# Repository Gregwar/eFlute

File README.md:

# eFlute

**WARNING: This is still a work in progress, which is really poorly documented and with uncertain release date and evolution**

## Video

[Here is a video of an old version of the flute](https://www.youtube.com/watch?v=Vu05FvypGyI)

## License

This project is under CC-BY-NC license. If you're not sure about what you can
do, you should ask the author Grégoire Passault (g.passault@gmail.com).

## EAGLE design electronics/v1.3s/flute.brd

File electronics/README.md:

# Electronics

Here are (eagle) files to build the PCB

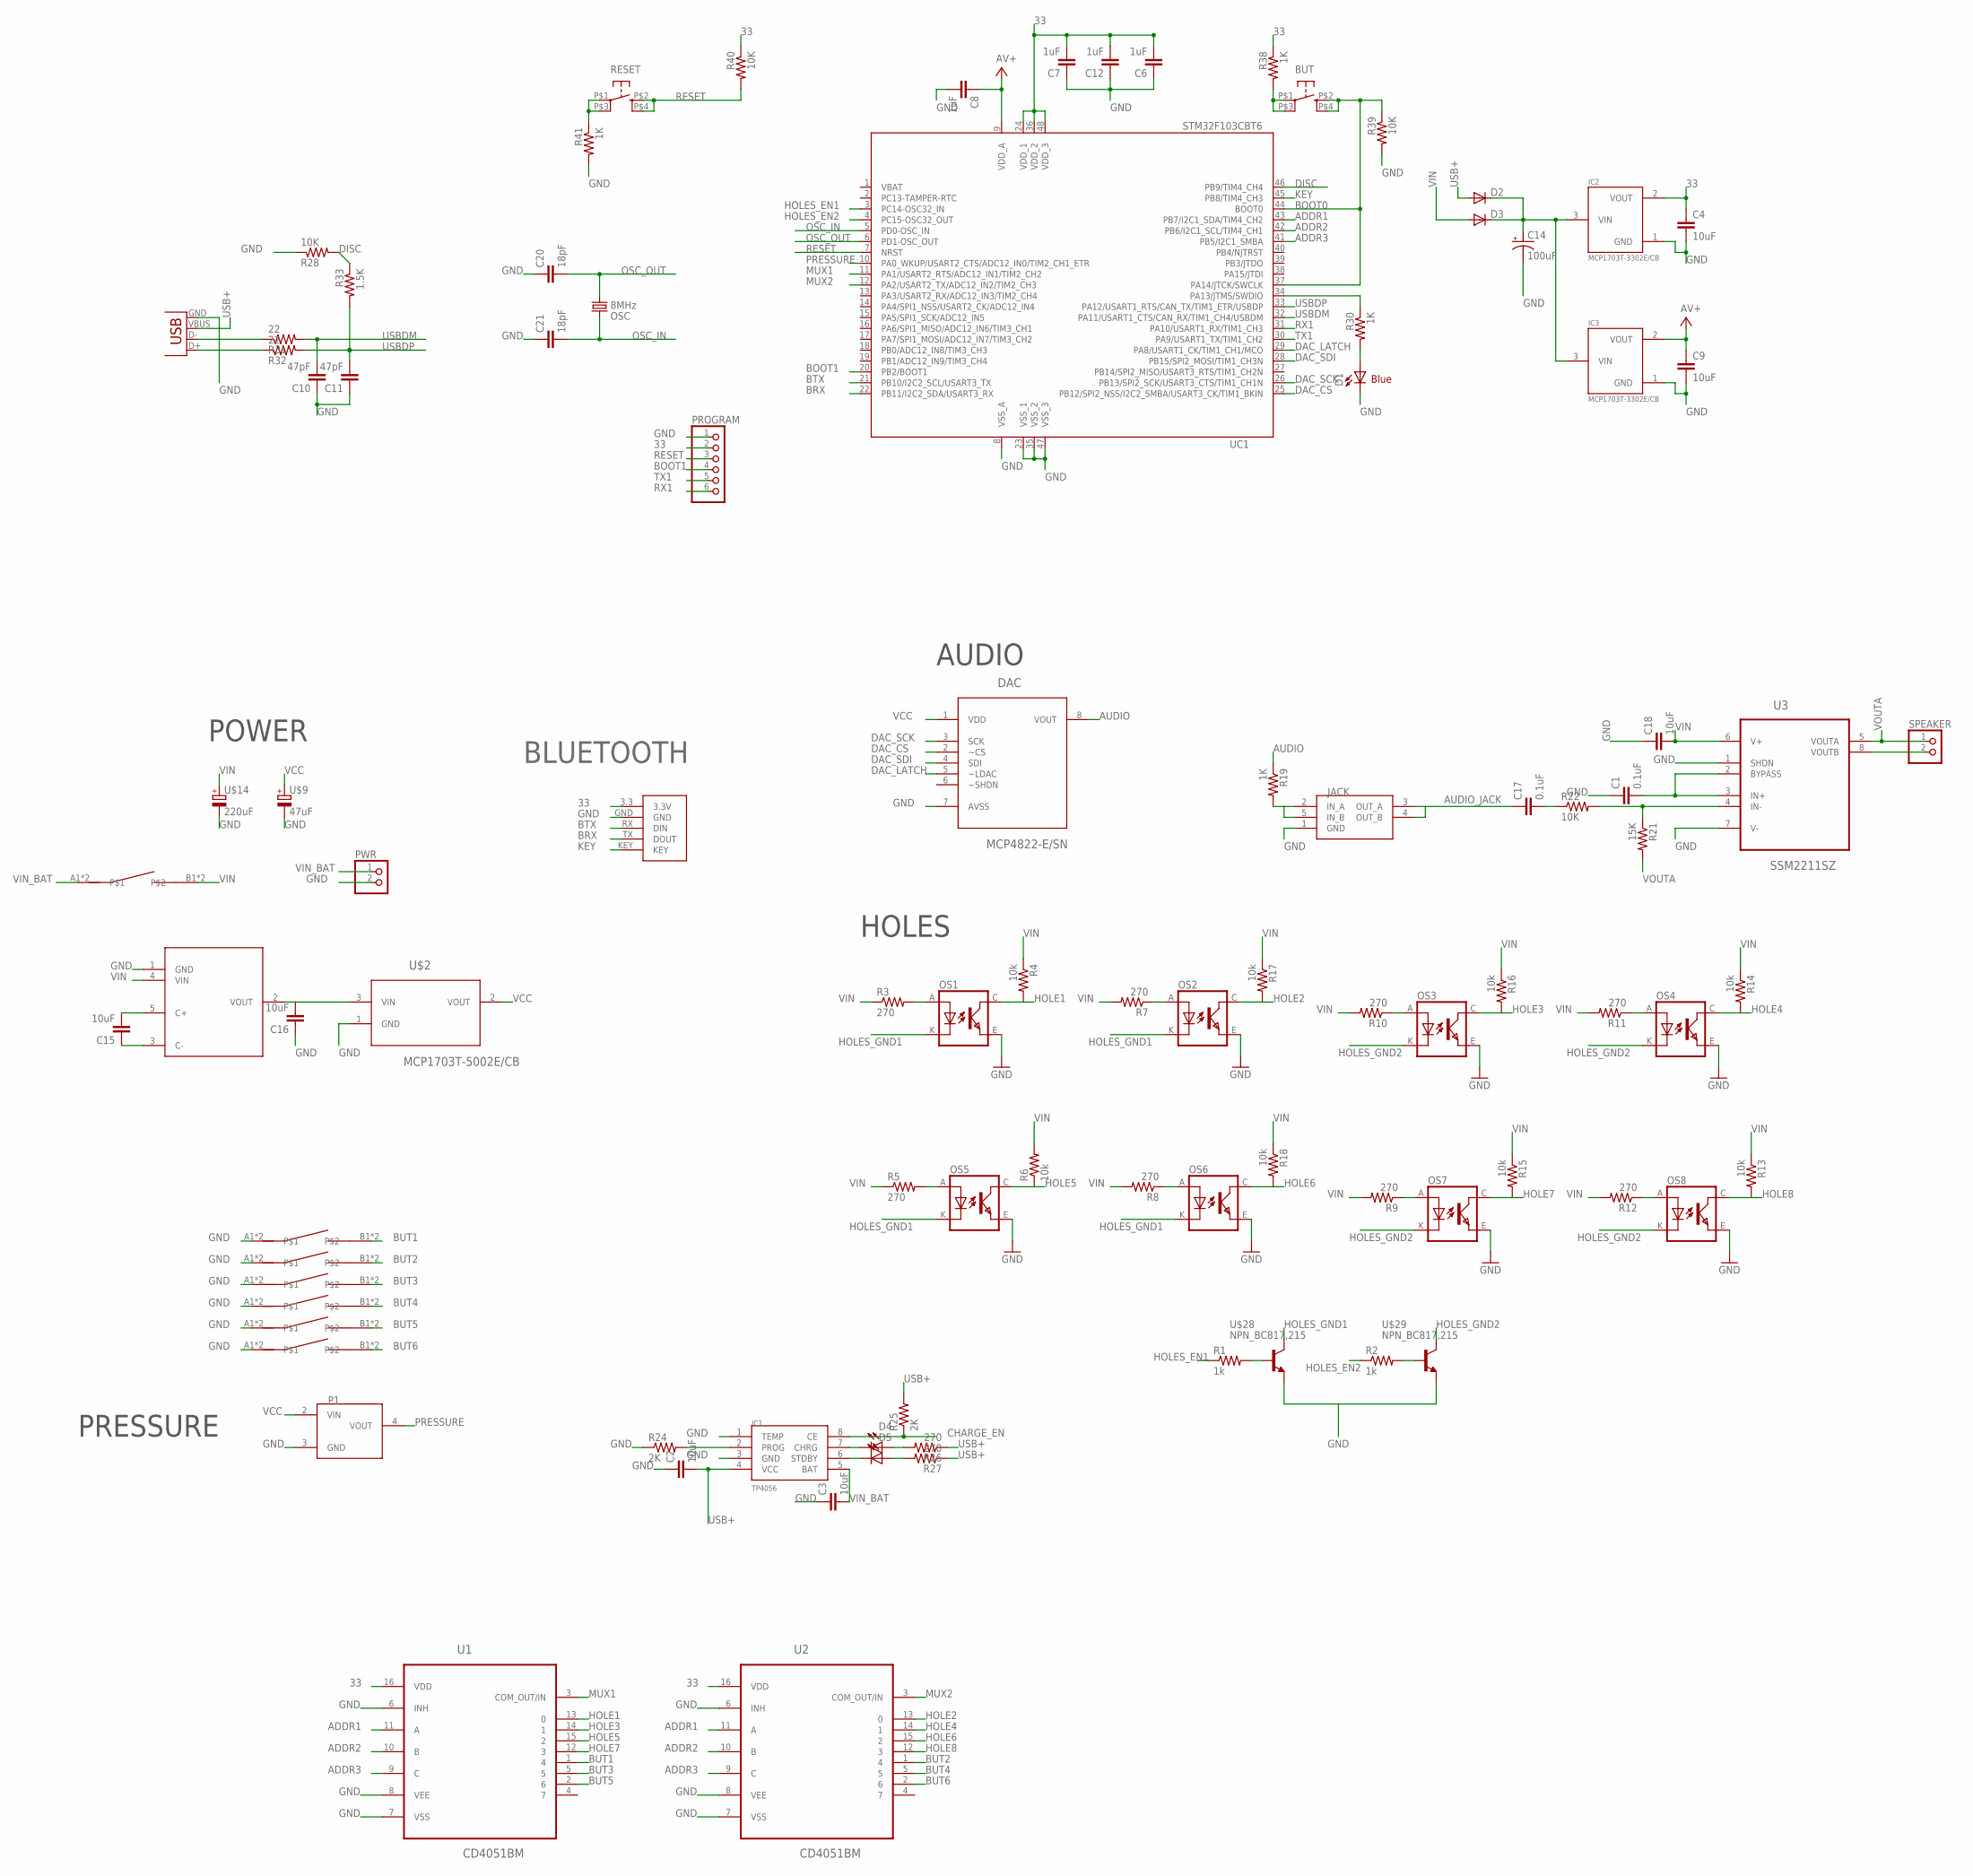
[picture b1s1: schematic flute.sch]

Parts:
BUT: KMR211GLFS; PUSHBUTTON-KMR241GLFS
C1, C17: 0.1uF; 0805
C2, C3, C4, C9, C15, C16, C18: 10uF; 0805
C6, C7, C8, C12: 1uF; 0805
C10, C11: 47pF; 0805
C14: 100uF; EIA3216
C20, C21: 18pF; 0805
D1: Blue; LED-1206
D2, D3: DIODESOD; SOD-323
D4: Red; LED-1206
D5: Green; LED-1206
DAC: MCP4822-E/SN; SOIC8-N_MC
IC1: TP4056; SOP-8
IC2, IC3: MCP1703T-3302E/CB; SOT23
JACK: JACK; 3F07
OS1, OS2, OS3, OS4, OS5, OS6, OS7, OS8: TCRT5000
OSC: 8MHz; CRYSTAL-SMD-5X3
P1: PRESSURE_SENSOR; MPXV5050GP
PROGRAM: CONNEC_1X066PADS; 6PADS
PWR: CONNEC_1X02BASIC; CONNEC_1X02
R1, R2: 1k; 0805
R3, R5, R7, R8, R9, R10, R11, R12, R26, R27: 270; 0805
R4, R6, R13, R14, R15, R16, R17, R18: 10k; 0805
R19, R30, R38, R41: 1K; 0805
R21: 15K; 0805
R22, R28, R39, R40: 10K; 0805
R24, R25: 2K; 0805
R31, R32: 22; 0805
R33: 1.5K; 0805
RESET: KMR211GLFS; PUSHBUTTON-KMR241GLFS
SPEAKER: CONNEC_1X02BASIC; CONNEC_1X02
U1, U2: CD4051BM; SOIC127P600X175-16N
U3: SSM2211SZ; SOIC127P600X175-8N
U$1: MAX1683; SOT23-5
U$2: MCP1703T-5002E/CB; SOT95P300X145-3N
U$9: 47uF; PANASONIC_D
U$14: 220uF; PANASONIC_D8
U$16: SWITCHKCD11; KCD11
U$18, U$19, U$20, U$21, U$22, U$23: SWITCH6X6X10; SWITCH_6X6X10
U$24: HC05; HC-05
U$28, U$29: NPN_BC817,215; SOT-23
UC1: STM32F103CBT6; LQFP48
X1: USB-MINIB

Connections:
32: BUT.P$2 (2), BUT.P$4 (4), R39.1, UC1.37 (PA14/JTCK/SWCLK), UC1.44 (BOOT0)
33: C4.1, C6.2, C7.2, C12.2, IC2.2 (VOUT), PROGRAM.2, R38.1, R40.1, U1.16 (VDD), U2.16 (VDD), U$24.3.3 (3.3V), UC1.24 (VDD_1), UC1.36 (VDD_2), UC1.48 (VDD_3)
ADDR1: U1.11 (A), U2.11 (A), UC1.43 (PB7/I2C1_SDA/TIM4_CH2)
ADDR2: U1.10 (B), U2.10 (B), UC1.42 (PB6/I2C1_SCL/TIM4_CH1)
ADDR3: U1.9 (C), U2.9 (C), UC1.41 (PB5/I2C1_SMBA)
AUDIO: DAC.8 (VOUT), R19.1
AUDIO_JACK: C17.1, JACK.3 (OUT_A), JACK.4 (OUT_B)
AV+: C8.1, C9.1, IC3.2 (VOUT), UC1.9 (VDD_A)
BOOT1: PROGRAM.4, UC1.20 (PB2/BOOT1)
BRX: U$24.TX (DOUT), UC1.22 (PB11/I2C2_SDA/USART3_RX)
BTX: U$24.RX (DIN), UC1.21 (PB10/I2C2_SCL/USART3_TX)
BUT1: U1.1 (4), U$18.B1, U$18.B2
BUT2: U2.1 (4), U$19.B1, U$19.B2
BUT3: U1.5, U$20.B1, U$20.B2
BUT4: U2.5, U$21.B1, U$21.B2
BUT5: U1.2 (6), U$22.B1, U$22.B2
BUT6: U2.2 (6), U$23.B1, U$23.B2
CHARGE_EN: IC1.8 (CE), R25.1
DAC_CS: DAC.2 (~CS), UC1.25 (PB12/SPI2_NSS/I2C2_SMBA/USART3_CK/TIM1_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)
DAC_LATCH: DAC.5 (~LDAC), UC1.29 (PA8/USART1_CK/TIM1_CH1/MCO)
DAC_SCK: DAC.3 (SCK), UC1.26 (PB13/SPI2_SCK/USART3_CTS/TIM1_CH1N)
DAC_SDI: DAC.4 (SDI), UC1.28 (PB15/SPI2_MOSI/TIM1_CH3N)
DISC: R28.2, R33.1, UC1.46 (PB9/TIM4_CH4)
GND: C1.1, C2.1, C3.1, C4.2, C6.1, C7.1, C8.2, C9.2, C10.1, C11.1, C12.1, C14.C (-), C16.1, C18.1, C20.1, C21.1, D1.C, DAC.7 (AVSS), IC1.1 (TEMP), IC1.3 (GND), IC2.1 (GND), IC3.1 (GND), JACK.1 (GND), OS1.E (EMITTER), OS2.E (EMITTER), OS3.E (EMITTER), OS4.E (EMITTER), OS5.E (EMITTER), OS6.E (EMITTER), OS7.E (EMITTER), OS8.E (EMITTER), P1.3 (GND), PROGRAM.1, PWR.2, R24.1, R28.1, R39.2, R41.2, U1.6 (INH), U1.7 (VSS), U1.8 (VEE), U2.6 (INH), U2.7 (VSS), U2.8 (VEE), U3.1 (SHDN), U3.7 (V-), U$1.1 (GND), U$2.1 (GND), U$9.-, U$14.-, U$18.A1, U$18.A2, U$19.A1, U$19.A2, U$20.A1, U$20.A2, U$21.A1, U$21.A2, U$22.A1, U$22.A2, U$23.A1, U$23.A2, U$24.GND, U$28.2 (E), U$29.2 (E), UC1.8 (VSS_A), UC1.23 (VSS_1), UC1.35 (VSS_2), UC1.47 (VSS_3), X1.GND
HOLE1: OS1.C (COLLECTOR), R4.2, U1.13 (0)
HOLE2: OS2.C (COLLECTOR), R17.2, U2.13 (0)
HOLE3: OS3.C (COLLECTOR), R16.2, U1.14 (1)
HOLE4: OS4.C (COLLECTOR), R14.2, U2.14 (1)
HOLE5: OS5.C (COLLECTOR), R6.1, U1.15 (2)
HOLE6: OS6.C (COLLECTOR), R18.2, U2.15 (2)
HOLE7: OS7.C (COLLECTOR), R15.2, U1.12 (3)
HOLE8: OS8.C (COLLECTOR), R13.2, U2.12 (3)
HOLES_EN1: R1.1, UC1.3 (PC14-OSC32_IN)
HOLES_EN2: R2.1, UC1.4 (PC15-OSC32_OUT)
HOLES_GND1: OS1.K (CATHODE), OS2.K (CATHODE), OS5.K (CATHODE), OS6.K (CATHODE), U$28.3 (C)
HOLES_GND2: OS3.K (CATHODE), OS4.K (CATHODE), OS7.K (CATHODE), OS8.K (CATHODE), U$29.3 (C)
KEY: U$24.KEY, UC1.45 (PB8/TIM4_CH3)
MUX1: U1.3 (COM_OUT/IN), UC1.11 (PA1/USART2_RTS/ADC12_IN1/TIM2_CH2)
MUX2: U2.3 (COM_OUT/IN), UC1.12 (PA2/USART2_TX/ADC12_IN2/TIM2_CH3)
unnamed: C1.2, U3.2 (BYPASS), U3.3 (IN+)
unnamed: R21.1, R22.2, U3.4 (IN-)
unnamed: R1.2, U$28.1 (B)
unnamed: R2.2, U$29.1 (B)
unnamed: OS1.A (ANODE), R3.2
unnamed: D5.A, R27.2
unnamed: OS2.A (ANODE), R7.1
unnamed: JACK.2 (IN_A), JACK.5 (IN_B), R19.2
unnamed: OS3.A (ANODE), R10.1
unnamed: C17.2, R22.1
unnamed: OS4.A (ANODE), R11.1
unnamed: SPEAKER.2, U3.8 (VOUTB)
unnamed: OS5.A (ANODE), R5.2
unnamed: OS6.A (ANODE), R8.1
unnamed: D4.A, R26.2
unnamed: OS7.A (ANODE), R9.1
unnamed: OS8.A (ANODE), R12.1
unnamed: IC1.2 (PROG), R24.2
unnamed: C15.1, U$1.3 (C-)
unnamed: D4.C, IC1.7 (CHRG)
unnamed: D5.C, IC1.6 (STDBY)
unnamed: BUT.P$1 (1), BUT.P$3 (3), R38.2
unnamed: R41.1, RESET.P$1 (1), RESET.P$3 (3)
unnamed: D1.A, R30.2
unnamed: R30.1, UC1.34 (PA13/JTMS/SWDIO)
unnamed: C15.2, U$1.5 (C+)
unnamed: C16.2, U$1.2 (VOUT), U$2.3 (VIN)
unnamed: R31.1, X1.D-
unnamed: R32.1, X1.D+
OSC_IN: C21.2, OSC.3 (2), UC1.5 (PD0-OSC_IN)
OSC_OUT: C20.2, OSC.1, UC1.6 (PD1-OSC_OUT)
PRESSURE: P1.4 (VOUT), UC1.10 (PA0_WKUP/USART2_CTS/ADC12_IN0/TIM2_CH1_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)
RESET: PROGRAM.3, R40.2, RESET.P$2 (2), RESET.P$4 (4), UC1.7 (NRST)
RX1: PROGRAM.6, UC1.31 (PA10/USART1_RX/TIM1_CH3)
TX1: PROGRAM.5, UC1.30 (PA9/USART1_TX/TIM1_CH2)
USB+: C2.2, D2.2 (A), IC1.4 (VCC), R25.2, R26.1, R27.1, X1.VBUS
USBDM: C10.2, R31.2, UC1.32 (PA11/USART1_CTS/CAN_RX/TIM1_CH4/USBDM)
USBDP: C11.2, R32.2, R33.2, UC1.33 (PA12/USART1_RTS/CAN_TX/TIM1_ETR/USBDP)
VBAT: UC1.1 (VBAT)
VCC: DAC.1 (VDD), P1.2 (VIN), U$2.2 (VOUT), U$9.+
VIN: C18.2, D3.2 (A), R3.1, R4.1, R5.1, R6.2, R7.2, R8.2, R9.2, R10.2, R11.2, R12.2, R13.1, R14.1, R15.1, R16.1, R17.1, R18.1, U3.6 (V+), U$1.4 (VIN), U$14.+, U$16.B1, U$16.B2
VIN_BAT: C3.2, IC1.5 (BAT), PWR.1, U$16.A1, U$16.A2
VIN_REGS: C14.A (+), D2.1 (C), D3.1 (C), IC2.3 (VIN), IC3.3 (VIN)
VOUTA: R21.2, SPEAKER.1, U3.5 (VOUTA)

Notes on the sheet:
POWER
PRESSURE
AUDIO
HOLES
BOOT0
Blue
BLUETOOTH

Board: 2 copper layers, 96 parts (9 on the bottom side), 82 nets, no tracks yet.

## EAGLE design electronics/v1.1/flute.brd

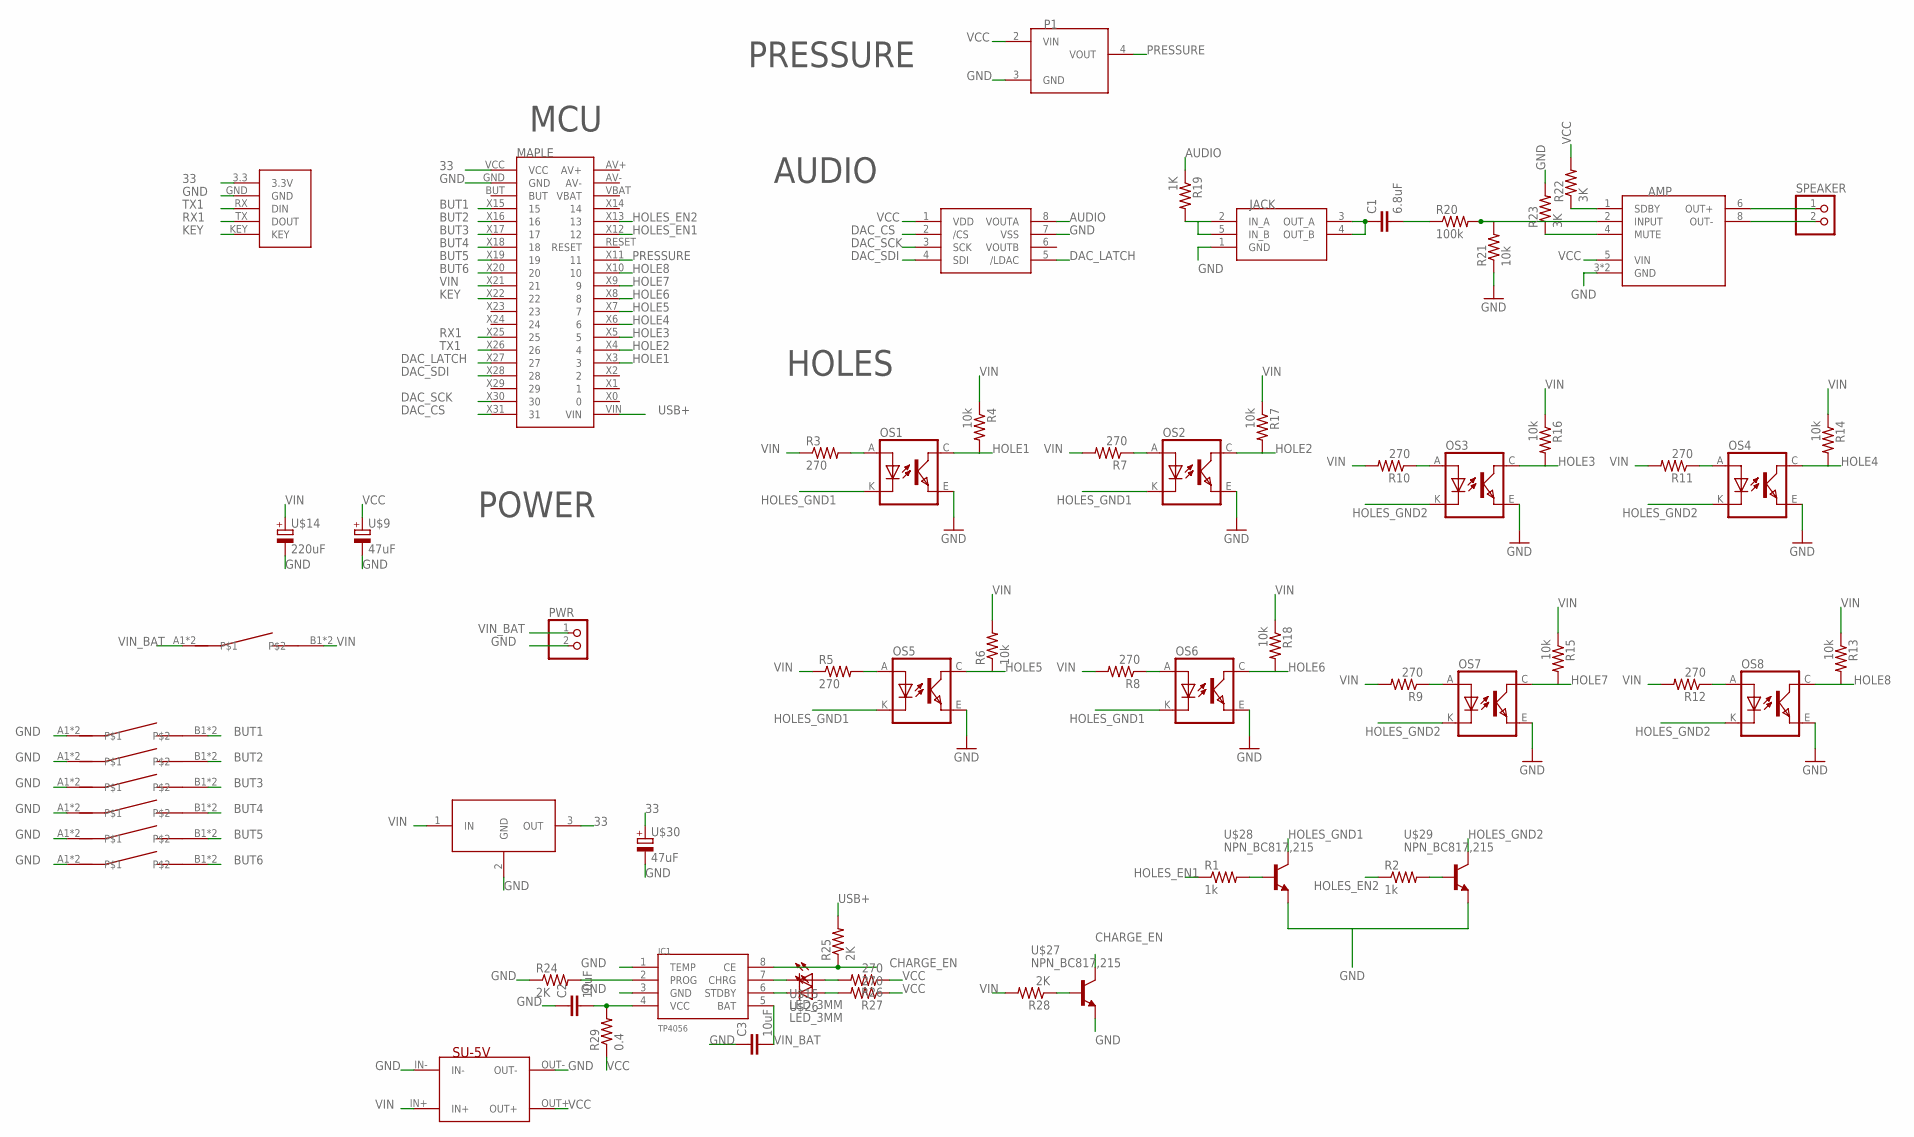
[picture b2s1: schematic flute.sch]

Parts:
AMP: AN7511DIP8; DIL08
C1: 6.8uF; 0805
C2, C3: 10uF; 0805
IC1: TP4056; SOP-8
JACK: JACK; 3F07
MAPLE: MAPLE_MINI; CONNEC_2X20
OS1, OS2, OS3, OS4, OS5, OS6, OS7, OS8: TCRT5000
P1: PRESSURE_SENSOR; MPXV5050GP
PWR: CONNEC_1X02BASIC; CONNEC_1X02
R1, R2: 1k; 0805
R3, R5, R7, R8, R9, R10, R11, R12, R26, R27: 270; 0805
R4, R6, R13, R14, R15, R16, R17, R18, R21: 10k; 0805
R19: 1K; 0805
R20: 100k; 0805
R22, R23: 3K; 0805
R24, R25, R28: 2K; 0805
R29: 0.4; 0805
SPEAKER: CONNEC_1X02BASIC; CONNEC_1X02
SU-5V: STEPUP-5V
U$9, U$30: 47uF; PANASONIC_D
U$14: 220uF; PANASONIC_D8
U$15, U$26: LED_3MM; LED3MM
U$16: SWITCHKCD11; KCD11
U$17: MCP4822; DIL08
U$18, U$19, U$20, U$21, U$22, U$23: SWITCH6X6X10; SWITCH_6X6X10
U$24: HC05; HC-05
U$25: MCP1703T-5002EDB; SOT223
U$27, U$28, U$29: NPN_BC817,215; SOT-23

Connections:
33: MAPLE.VCC, U$24.3.3 (3.3V), U$25.3 (OUT), U$30.+
AUDIO: R19.1, U$17.8 (VOUTA)
BUT1: MAPLE.X15 (15), U$18.B1, U$18.B2
BUT2: MAPLE.X16 (16), U$19.B1, U$19.B2
BUT3: MAPLE.X17 (17), U$20.B1, U$20.B2
BUT4: MAPLE.X18 (18), U$21.B1, U$21.B2
BUT5: MAPLE.X19 (19), U$22.B1, U$22.B2
BUT6: MAPLE.X20 (20), U$23.B1, U$23.B2
CHARGE_EN: IC1.8 (CE), R25.1, U$27.3 (C)
DAC_CS: MAPLE.X31 (31), U$17.2 (/CS)
DAC_LATCH: MAPLE.X27 (27), U$17.5 (/LDAC)
DAC_SCK: MAPLE.X30 (30), U$17.3 (SCK)
DAC_SDI: MAPLE.X28 (28), U$17.4 (SDI)
GND: AMP.3 (GND), AMP.7 (GND), C2.1, C3.1, IC1.1 (TEMP), IC1.3 (GND), JACK.1 (GND), MAPLE.GND, OS1.E (EMITTER), OS2.E (EMITTER), OS3.E (EMITTER), OS4.E (EMITTER), OS5.E (EMITTER), OS6.E (EMITTER), OS7.E (EMITTER), OS8.E (EMITTER), P1.3 (GND), PWR.2, R21.1, R23.2, R24.1, SU-5V.IN-, SU-5V.OUT-, U$9.-, U$14.-, U$17.7 (VSS), U$18.A1, U$18.A2, U$19.A1, U$19.A2, U$20.A1, U$20.A2, U$21.A1, U$21.A2, U$22.A1, U$22.A2, U$23.A1, U$23.A2, U$24.GND, U$25.2 (GND), U$27.2 (E), U$28.2 (E), U$29.2 (E), U$30.-
HOLE1: MAPLE.X3 (3), OS1.C (COLLECTOR), R4.2
HOLE2: MAPLE.X4 (4), OS2.C (COLLECTOR), R17.2
HOLE3: MAPLE.X5 (5), OS3.C (COLLECTOR), R16.2
HOLE4: MAPLE.X6 (6), OS4.C (COLLECTOR), R14.2
HOLE5: MAPLE.X7 (7), OS5.C (COLLECTOR), R6.1
HOLE6: MAPLE.X8 (8), OS6.C (COLLECTOR), R18.2
HOLE7: MAPLE.X9 (9), OS7.C (COLLECTOR), R15.2
HOLE8: MAPLE.X10 (10), OS8.C (COLLECTOR), R13.2
HOLES_EN1: MAPLE.X12 (12), R1.1
HOLES_EN2: MAPLE.X13 (13), R2.1
HOLES_GND1: OS1.K (CATHODE), OS2.K (CATHODE), OS5.K (CATHODE), OS6.K (CATHODE), U$28.3 (C)
HOLES_GND2: OS3.K (CATHODE), OS4.K (CATHODE), OS7.K (CATHODE), OS8.K (CATHODE), U$29.3 (C)
KEY: MAPLE.X22 (22), U$24.KEY
unnamed: AMP.6 (OUT+), SPEAKER.1
unnamed: AMP.8 (OUT-), SPEAKER.2
unnamed: R1.2, U$28.1 (B)
unnamed: R2.2, U$29.1 (B)
unnamed: OS1.A (ANODE), R3.2
unnamed: R27.2, U$26.A
unnamed: OS2.A (ANODE), R7.1
unnamed: JACK.2 (IN_A), JACK.5 (IN_B), R19.2
unnamed: OS3.A (ANODE), R10.1
unnamed: AMP.4 (MUTE), R23.1
unnamed: OS4.A (ANODE), R11.1
unnamed: C1.2, R20.1
unnamed: OS5.A (ANODE), R5.2
unnamed: AMP.1 (SDBY), R22.1
unnamed: OS6.A (ANODE), R8.1
unnamed: R26.2, U$15.A
unnamed: OS7.A (ANODE), R9.1
unnamed: AMP.2 (INPUT), R20.2, R21.2
unnamed: OS8.A (ANODE), R12.1
unnamed: C1.1, JACK.3 (OUT_A), JACK.4 (OUT_B)
unnamed: IC1.2 (PROG), R24.2
unnamed: R28.1, U$27.1 (B)
unnamed: C2.2, IC1.4 (VCC), R29.2
unnamed: IC1.7 (CHRG), U$15.K (C)
unnamed: IC1.6 (STDBY), U$26.K (C)
PRESSURE: MAPLE.X11 (11), P1.4 (VOUT)
RX1: MAPLE.X25 (25), U$24.TX (DOUT)
TX1: MAPLE.X26 (26), U$24.RX (DIN)
USB+: MAPLE.VIN, R25.2
VCC: AMP.5 (VIN), P1.2 (VIN), R22.2, R26.1, R27.1, R29.1, SU-5V.OUT+, U$9.+, U$17.1 (VDD)
VIN: MAPLE.X21 (21), R3.1, R4.1, R5.1, R6.2, R7.2, R8.2, R9.2, R10.2, R11.2, R12.2, R13.1, R14.1, R15.1, R16.1, R17.1, R18.1, R28.2, SU-5V.IN+, U$14.+, U$16.B1, U$16.B2, U$25.1 (IN)
VIN_BAT: C3.2, IC1.5 (BAT), PWR.1, U$16.A1, U$16.A2

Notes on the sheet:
POWER
MCU
PRESSURE
AUDIO
HOLES

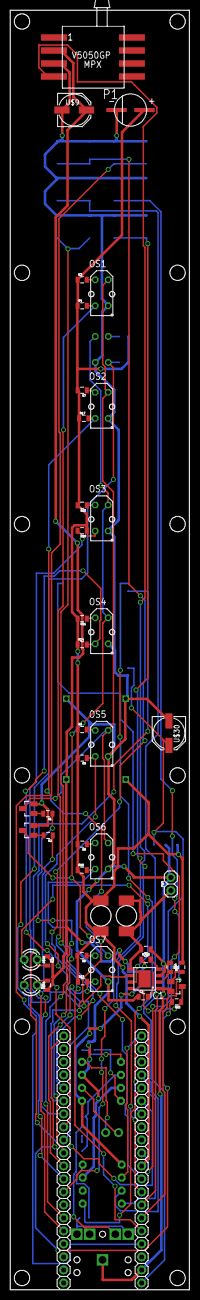
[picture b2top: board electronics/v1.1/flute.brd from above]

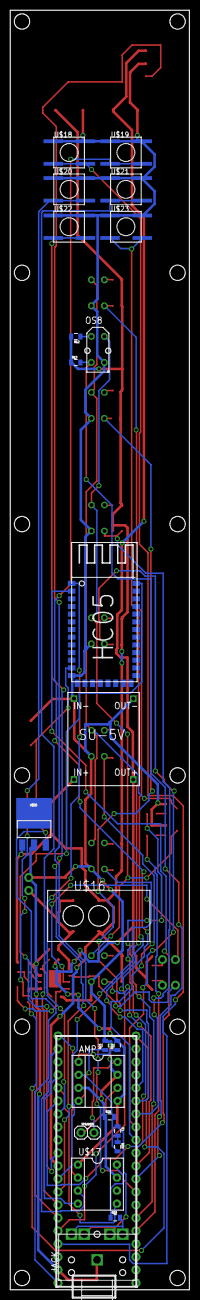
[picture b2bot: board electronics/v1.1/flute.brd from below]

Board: 2 copper layers, 35.0 x 250.0 mm, 78 parts (23 on the bottom side), 59 nets.

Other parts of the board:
U$1, U$2, U$3, U$4, U$5, U$6, U$7, U$8, U$10, U$11, U$12, U$13: M3_HOLE

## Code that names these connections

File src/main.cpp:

#include <stdlib.h>
#include <wirish/wirish.h>
#include <servos.h>
#include <terminal.h>
#include <main.h>
#include <SdFat.h>
#include "Balance.h"

#define HOLE1       3
#define HOLE2       4
#define HOLE3       5
#define HOLE4       6
#define HOLE5       7
#define HOLE6       8
#define HOLE7       9
#define HOLE8       10
#define HOLES_EN    2

Balance blow(22, 21);

TERMINAL_COMMAND(tare, "Tare")
{
    blow.tare();
    while (blow.taring) {
        blow.tick();
    }
}

TERMINAL_COMMAND(blow, "Blow test")
{
    while (!SerialUSB.available()) {
        terminal_io()->println(blow.sample());
    }
}

// Sign an expression
#define VALUE_SIGN(value, length) \
    ((value < (1<<(length-1))) ? \
    (value) \
    : (value-(1<<length)))

TERMINAL_PARAMETER_INT(vol, "Volume", 100);

bool playing = false;
HardwareSPI spi(1);
Sd2Card card;
SdVolume volume;
SdFile root;
SdFile file;

class DAC
{
    public:
        DAC(int cs_, int spiNum, int latchPin_)
            : spi(spiNum), latchPin(latchPin_), cs(cs_)
        {
            pinMode(latchPin, OUTPUT);
            digitalWrite(latchPin, HIGH);
            spi.begin(SPI_18MHZ, MSBFIRST, 0);
            pinMode(cs, OUTPUT);
            digitalWrite(cs, HIGH);
        }

        void set(int value)
        {
            value |= (1<<12);
            // value |= (1<<13);
            digitalWrite(cs, LOW);
            spi.send((value>>8)&0xff);
            spi.send((value>>0)&0xff);
            digitalWrite(cs, HIGH);
        }

        void latch()
        {
            digitalWrite(latchPin, LOW);
            digitalWrite(latchPin, HIGH);
        }

        HardwareSPI spi;
        int latchPin;
        int cs;
};

DAC dac(31, 2, 27);

TERMINAL_COMMAND(dac, "dac set")
{
    if (argc != 1) {
        terminal_io()->println("Usage: dac [value]");
    } else {
        int value = atoi(argv[0]);
        dac.set(value);
        dac.latch();
    }
}

#include "sin.h"

TERMINAL_COMMAND(sin, "Sinus")
{
    float amp = atof(argv[0]);
    float samp = 0;
    int i = 0;
    while (!SerialUSB.available()) {
//        samp = 0.995*samp+0.005*amp;
        i++;
        if (i >= 50) i = 0;
        dac.set(values[i]*(samp/2)+2000);
        dac.latch();
        if (blow.dataAvailable()) {
            samp = (blow.read()-blow.zero)/100;
            delay_us(1);
        } else {
            delay_us(6);
        }
    }
    /*
    while (samp > 0.01) {
        samp = 0.995*samp;
        i++;
        if (i >= 50) i = 0;
        dac.set(values[i]*(samp/2)+2000);
        dac.latch();
        delay_us(6);
    }
    */
}

#define SAMPLES_BUF 512
int samples1[SAMPLES_BUF];
int samples2[SAMPLES_BUF];
int samples_buffer = 1;
int samples_position = 0;
bool should_fill = false;

void interrupt()
{
    dac.latch();
    if (samples_position < 0) {
        samples_position = SAMPLES_BUF-1;
        should_fill = true;
        if (samples_buffer == 1) {
            samples_buffer = 2;
        } else {
            samples_buffer = 1;
        }
    }
    if (samples_buffer == 1) {
        dac.set(2000+(samples1[samples_position--]/(16000/vol)));
    } else {
        dac.set(2000+(samples2[samples_position--]/(16000/vol)));
    }
}

void fillBuffer(int *samples)
{
    char buffer[SAMPLES_BUF*2];
    file.read(buffer, SAMPLES_BUF*2);

    for (int k=0; k<SAMPLES_BUF; k++) {
        int sample = (buffer[2*k]&0xff);
        sample |= (buffer[2*k+1]&0xff)<<8;
        sample = VALUE_SIGN(sample, 16);
        samples[SAMPLES_BUF-k-1] = sample;
    }
}

void populateSamples()
{
    if (should_fill) {
        should_fill = false;
        if (samples_buffer == 1) {
            fillBuffer(samples2);
        } else {
            fillBuffer(samples1);
        }
    }
}

TERMINAL_COMMAND(sd, "Sd init")
{
    spi.begin(SPI_18MHZ, MSBFIRST, 0);
    if (card.init(&spi)) {
        terminal_io()->println("Success in card init");
        delay(100);
        if (volume.init(&card,1)) {
            terminal_io()->println("Volume mounted");
            if (root.openRoot(&volume)) {
                terminal_io()->println("Root opened");
            }
        }
    }
}

TERMINAL_COMMAND(play, "Play a sound")
{
    if (argc != 1) {
        terminal_io()->println("Usage: play sound.raw");
    } else {
        playing = false;
        if (file.isOpen()) file.close();
        if (file.open(&root, argv[0], O_READ)) {
            HardwareTimer timer(1);
            timer.pause();
            timer.setPrescaleFactor(1);
            timer.setOverflow(2250);
            timer.setCompare(TIMER_CH1, 1);
            timer.attachCompare1Interrupt(interrupt);
            timer.refresh();
            timer.resume();

            playing = true;

            /*
            for (int k=0; k<64; k++) {
                terminal_io()->println((int)getSample());
            }
            */
        }
    }
}

TERMINAL_COMMAND(holes, "Holes")
{
    digitalWrite(HOLES_EN, HIGH);
    terminal_io()->println(analogRead(HOLE1));
    terminal_io()->println(analogRead(HOLE2));
    terminal_io()->println(analogRead(HOLE3));
    terminal_io()->println(analogRead(HOLE4));
    terminal_io()->println(analogRead(HOLE5));
    terminal_io()->println(analogRead(HOLE6));
    terminal_io()->println(analogRead(HOLE7));
    terminal_io()->println(analogRead(HOLE8));
}

/**
 * Setup function
 */
void setup()
{
    blow.init();

    // For sd card
    afio_remap(AFIO_REMAP_SPI1);

    // Holes
    pinMode(HOLES_EN, OUTPUT);
    digitalWrite(HOLES_EN, LOW);
    pinMode(HOLE1, INPUT_FLOATING);
    pinMode(HOLE2, INPUT_FLOATING);
    pinMode(HOLE3, INPUT_FLOATING);
    pinMode(HOLE4, INPUT_FLOATING);
    pinMode(HOLE5, INPUT_FLOATING);
    pinMode(HOLE6, INPUT_FLOATING);
    pinMode(HOLE7, INPUT_FLOATING);
    pinMode(HOLE8, INPUT_FLOATING);

    terminal_init(&SerialUSB);
}

/**
 * Loop function
 */
void loop()
{
    terminal_tick();

    if (playing) {
        populateSamples();

        if (blow.dataAvailable()) {
            int tmp = (blow.sample()-24);
            if (tmp < 0) tmp = 0;
            if (tmp > 1000) tmp = 1000;
            vol = 0.8*vol+0.2*tmp;
        }
    }
}

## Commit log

2015-08-10 Electronics model
2015-08-10 Code
2015-08-10 Ignore
2015-08-10 Electronics
2015-08-10 Renaming src to firmware
2015-08-21 Filtering blow
2015-08-22 v0.001
2015-08-24 echoing
2015-08-24 static sized dyn samples
2015-09-12 Fixes, optimizing notes
2015-09-12 transpose
2015-09-12 Makefile: removing useless
2015-09-12 Inhale on-the-go
2015-09-15 Rhoban
2015-09-16 tweak
2015-09-21 DAC -class
2015-11-03 Starting V1
2015-11-04 v1.01
2015-11-04 Routed V1 (to be checked)
2015-11-06 jack
2015-12-27 Fixes
2015-12-28 v1 (wip)
2015-12-28 v1 mecha (wip)
2016-01-02 flute
2016-01-12 Bottom plat
2016-01-12 chassis
2016-01-12 coffrage piles
2016-01-16 1.5/1.5
2016-01-16 v1.1
2016-01-18 holes
2016-01-20 Holes M3, better footprint for buttons
2016-01-20 elec
2016-01-21 elec v1.1 (wip)
2016-04-14 AMP SSM2211
2016-04-15 Version simplified
2016-04-17 v1.2
2016-05-09 Fixing resistor place
2016-06-08 BT & fixes for v1.2
2016-06-09 Adapting to elec 1.2s
2016-07-22 Reducing optical leds power consumption
2017-03-16 Prepare.sh
2017-03-16 CC BY NC
2017-03-20 electronics & readme
2017-03-20 3d tweaking folder
2017-03-22 3d update
2017-03-22 Renaming to en mouthpiece
2017-03-22 Updating names
2017-03-22 README
2017-03-22 Missing img

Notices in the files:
parts and their libraries:
SparkFun-Passives: Licensing: CC v3.0 Share-Alike You are welcome to use this library for commercial purposes.
